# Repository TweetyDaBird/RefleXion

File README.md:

# RefleXion
 Ortho Split Keyboard

 -------------

This is a joint project with concept by The Reflex (Pedro Quaresma), and design by TweetyDaBird (Markus Knutsson).

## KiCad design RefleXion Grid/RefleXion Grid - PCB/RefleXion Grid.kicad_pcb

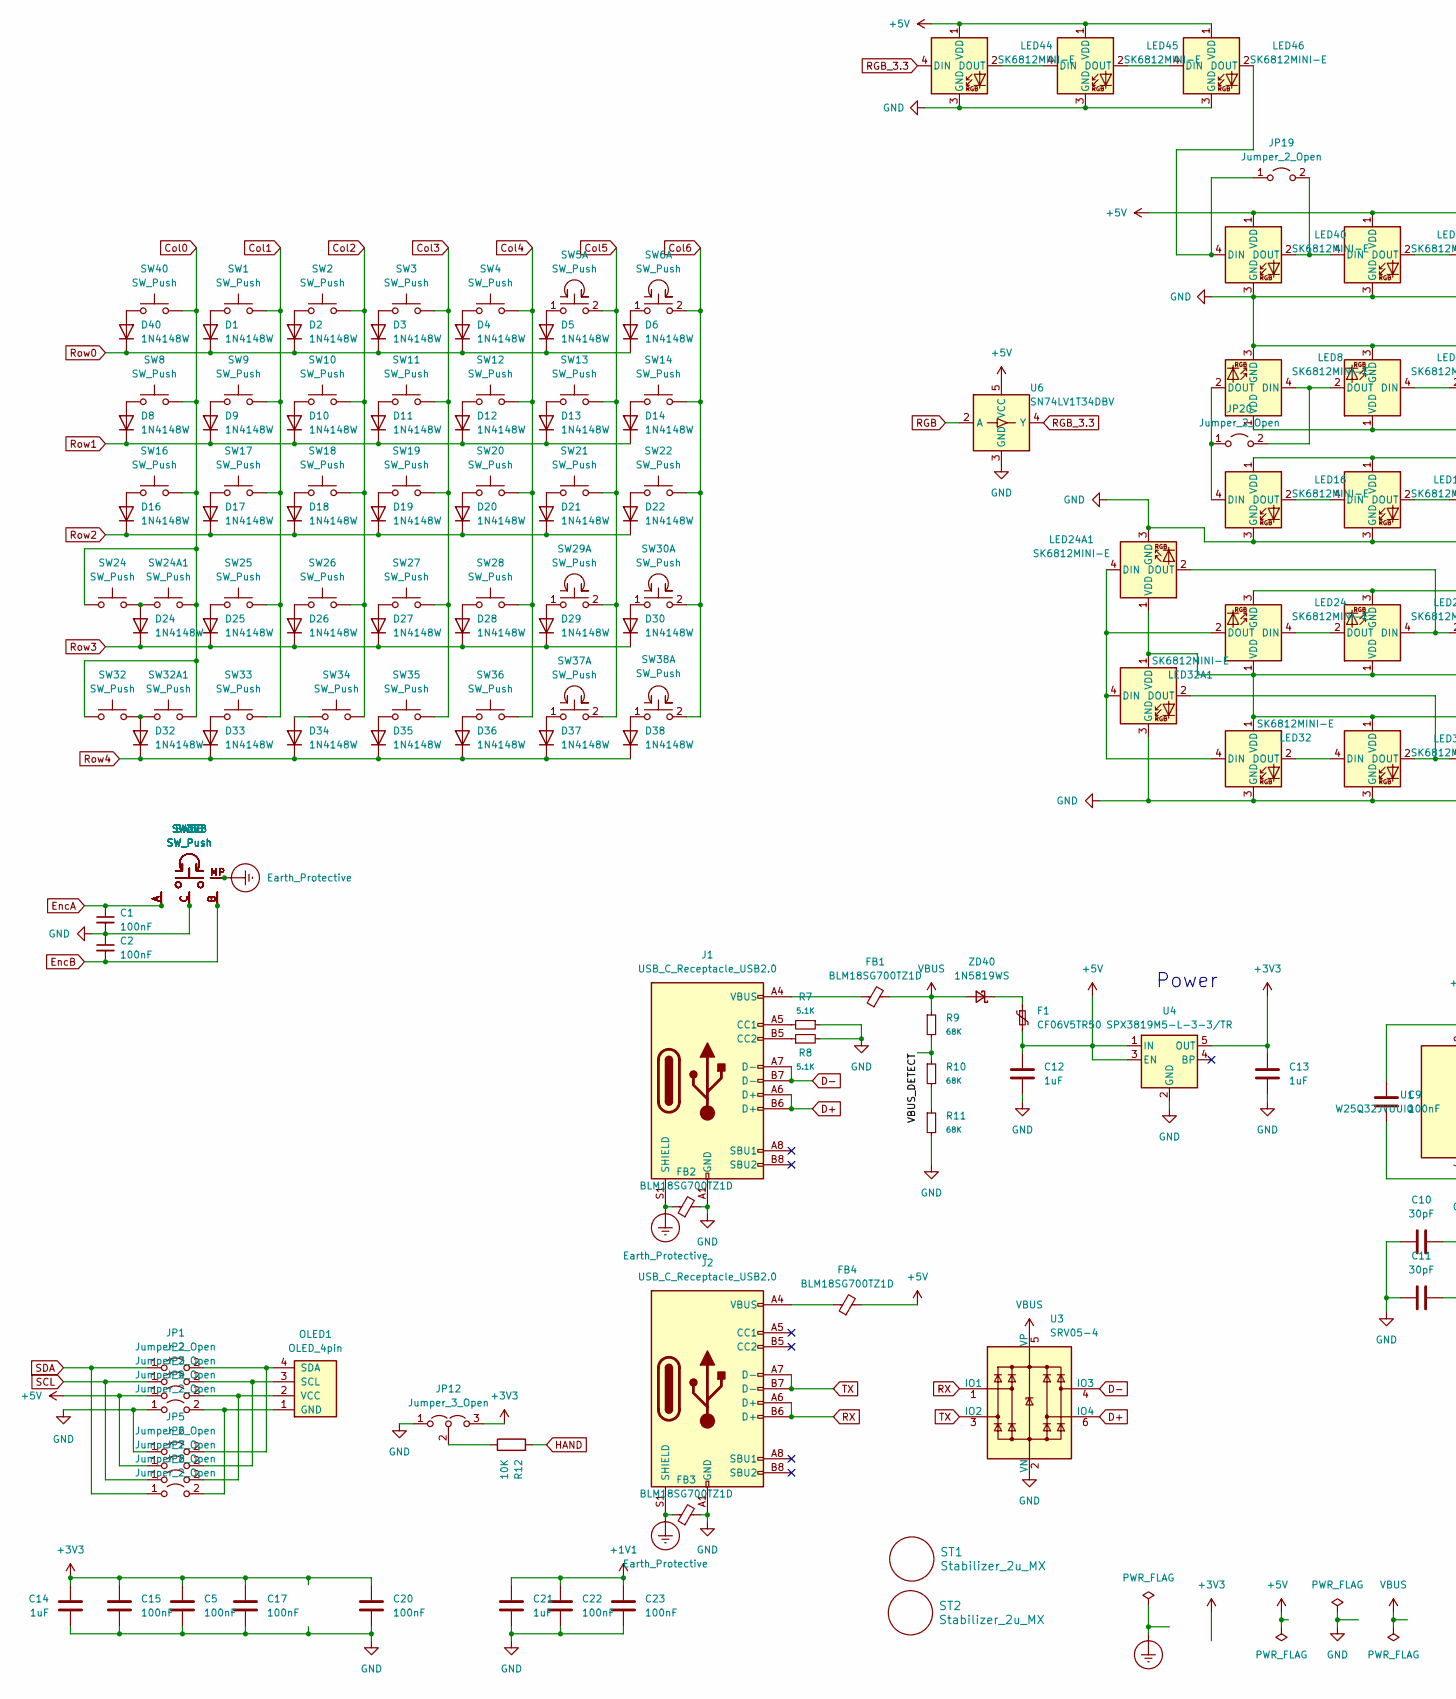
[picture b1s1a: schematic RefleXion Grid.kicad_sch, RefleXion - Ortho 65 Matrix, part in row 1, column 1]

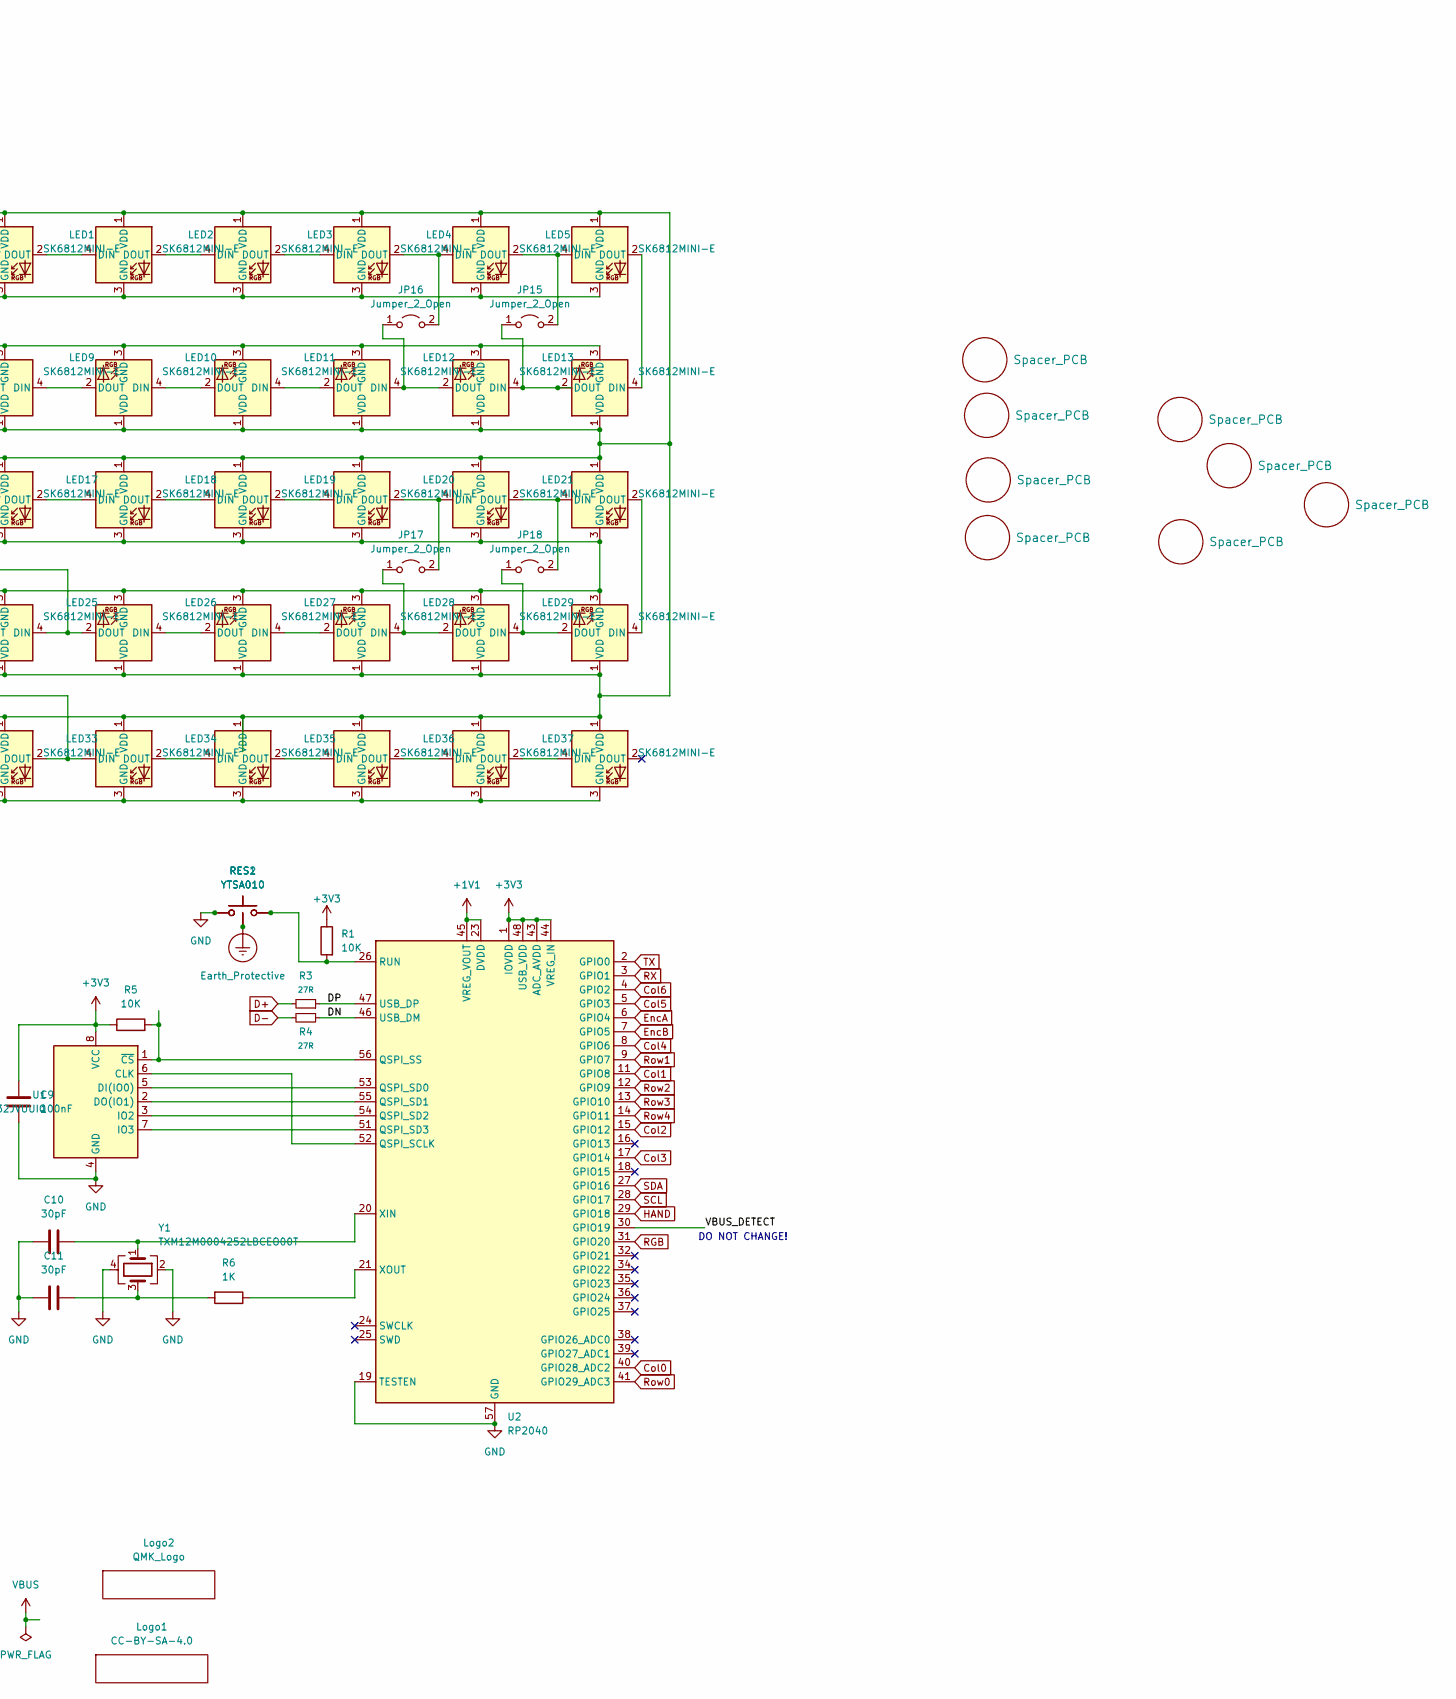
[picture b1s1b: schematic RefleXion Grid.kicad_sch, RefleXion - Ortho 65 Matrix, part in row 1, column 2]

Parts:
C1, C2: 100nF; C_0402_1005Metric
C5, C9, C15, C17, C20, C22, C23: 100nF; C_0402_1005Metric; LCSC C513772
C10, C11: 30pF; C_0402_1005Metric
C12, C13, C14, C21: 1uF; C_0402_1005Metric
D1, D2, D3, D4, D5, D6, D8, D9, D10, D11, D12, D13, D14, D16, D17, D18, D19, D20, D21, D22, D24, D25, D26, D27, D28, D29, D30, D32, D33, D34, D35, D36, D37, D38, D40: 1N4148W; D_SOD-123
F1: CF06V5TR50; R_0603_1608Metric; LCSC C163116
FB1, FB2, FB3, FB4: BLM18SG700TZ1D; C_0603_1608Metric_Pad1.08x0.95mm_HandSolder; LCSC C882974
H1, H2, H3, H4, H6, H7, H8, H9: Spacer_PCB; Spacer PCB hole
J1, J2: USB_C_Receptacle_USB2.0; Molex-216990_GCT-USB45xx_HRO-TYPE-C-31-M-13x-PiMicro; LCSC C165948
JP1, JP2, JP3, JP4, JP5, JP6, JP7, JP8, JP15, JP16, JP17, JP18, JP19, JP20: Jumper_2_Open; Jumper_min_v2
JP12: Jumper_3_Open; SolderJumper-3_open_mini
LED1, LED2, LED3, LED4, LED5, LED6, LED8, LED9, LED10, LED11, LED12, LED13, LED14, LED16, LED17, LED18, LED19, LED20, LED21, LED22, LED24, LED24A1, LED25, LED26, LED27, LED28, LED29, LED30, LED32, LED32A1, LED33, LED34, LED35, LED36, LED37, LED38, LED40, LED44, LED45, LED46: SK6812MINI-E; MX_SK6812MINI-E_REVERSIBLE_SMALL_PAD
Logo1: CC-BY-SA-4.0; CC_BY_SA_40_line
Logo2: QMK_Logo; Powered_by_QMK
OLED1: OLED_4pin; SSD1306-0.91-OLED-4pin-128x32
R1, R5: 10K; R_0402_1005Metric; LCSC C2078429
R3, R4: 27R; R_0402_1005Metric; LCSC C1701143
R6: 1K; R_0402_1005Metric; LCSC C2139907
R7, R8: 5.1K; R_0402_1005Metric; LCSC C2075916
R9, R10, R11: 68K; R_0402_1005Metric; LCSC C2075916
R12: 10K; R_0402_1005Metric; LCSC C2139907
RES1, RES2: YTSA010; YTS-A002; LCSC C2888934
ST1, ST2: Stabilizer_2u_MX; Stabilizer_Cherry_MX_2.00u
SW1, SW2, SW3, SW4, SW8, SW9, SW10, SW11, SW12, SW13, SW14, SW16, SW17, SW18, SW19, SW20, SW21, SW22, SW24, SW24A1, SW25, SW26, SW27, SW28, SW32, SW32A1, SW33, SW34, SW35, SW36, SW40: SW_Push; SW_MX_HotSwap_Reversible
SW5, SW6, SW29, SW30, SW37, SW38: SW_Push; SW_MX_HotSwap_Reversible_Encoder
U1: W25Q32JVUUIQ; USON-8_4x3mm_P0.8mm; LCSC C2999380
U2: RP2040; QFN-56-1EP_7x7mm_P0.4mm_EP3.2x3.2mm_ThermalVias; LCSC C2040
U3: SRV05-4; SOT-23-6; LCSC C558418
U4: SPX3819M5-L-3-3/TR; SOT-23-5; LCSC C9055
U6: SN74LV1T34DBV; SOT-23-5; LCSC C100024
Y1: TXM12M0004252LBCEO00T; Crystal_SMD_2520-4Pin_2.5x2.0mm; PartNo C284156; LCSC C284156
ZD40: 1N5819WS; D_SOD-323F

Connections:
+1V1: C21.1, C22.1, C23.1, U2.23 (DVDD), U2.45 (VREG_VOUT), U2.50 (DVDD)
+3V3: C5.1, C9.1, C13.1, C14.1, C15.1, C17.1, C20.1, JP12.3 (B), R1.1, R5.1, U1.8 (VCC), U2.1 (IOVDD), U2.10 (IOVDD), U2.22 (IOVDD), U2.33 (IOVDD), U2.42 (IOVDD), U2.43 (ADC_AVDD), U2.44 (VREG_IN), U2.48 (USB_VDD), U2.49 (IOVDD), U4.5 (OUT)
+5V: C12.1, F1.2, FB4.2, JP3.1 (A), JP6.1 (A), LED1.1 (VDD), LED2.1 (VDD), LED3.1 (VDD), LED4.1 (VDD), LED5.1 (VDD), LED6.1 (VDD), LED8.1 (VDD), LED9.1 (VDD), LED10.1 (VDD), LED11.1 (VDD), LED12.1 (VDD), LED13.1 (VDD), LED14.1 (VDD), LED16.1 (VDD), LED17.1 (VDD), LED18.1 (VDD), LED19.1 (VDD), LED20.1 (VDD), LED21.1 (VDD), LED22.1 (VDD), LED24.1 (VDD), LED24A1.1 (VDD), LED25.1 (VDD), LED26.1 (VDD), LED27.1 (VDD), LED28.1 (VDD), LED29.1 (VDD), LED30.1 (VDD), LED32.1 (VDD), LED32A1.1 (VDD), LED33.1 (VDD), LED34.1 (VDD), LED35.1 (VDD), LED36.1 (VDD), LED37.1 (VDD), LED38.1 (VDD), LED40.1 (VDD), LED44.1 (VDD), LED45.1 (VDD), LED46.1 (VDD), U4.1 (IN), U4.3 (EN), U6.5 (VCC)
/DN: R4.1, U2.46 (USB_DM)
/DP: R3.1, U2.47 (USB_DP)
/VBUS_DETECT: R9.2, R10.1, U2.30 (GPIO19)
Col0: SW8.1, SW16.1, SW24.1, SW24A1.1, SW32.1, SW32A1.1, SW40.1, U2.40 (GPIO28_ADC2)
Col1: SW1.2, SW9.2, SW17.2, SW25.2, SW33.2, U2.11 (GPIO8)
Col2: SW2.2, SW10.2, SW18.2, SW26.2, SW34.2, U2.15 (GPIO12)
Col3: SW3.2, SW11.2, SW19.2, SW27.2, SW35.2, U2.17 (GPIO14)
Col4: SW4.2, SW12.2, SW20.2, SW28.2, SW36.2, U2.8 (GPIO6)
Col5: SW5.2, SW13.2, SW21.2, SW29.2, SW37.2, U2.5 (GPIO3)
Col6: SW6.2, SW14.2, SW22.2, SW30.2, SW38.2, U2.4 (GPIO2)
D+: J1.A6 (D+), J1.B6 (D+), R3.2, U3.6 (IO4)
D-: J1.A7 (D-), J1.B7 (D-), R4.2, U3.4 (IO3)
Earth_Protective: FB2.1, FB3.1, J1.S1 (SHIELD), J2.S1 (SHIELD), RES1.3, RES2.3, SW5.MP, SW6.MP, SW29.MP, SW30.MP, SW37.MP, SW38.MP
EncA: C1.1, SW5.A, SW6.A, SW29.A, SW30.A, SW37.A, SW38.A, U2.6 (GPIO4)
EncB: C2.2, SW5.B, SW6.B, SW29.B, SW30.B, SW37.B, SW38.B, U2.7 (GPIO5)
GND: C1.2, C2.1, C5.2, C9.2, C10.2, C11.2, C12.2, C13.2, C14.2, C15.2, C17.2, C20.2, C21.2, C22.2, C23.2, FB2.2, FB3.2, J1.A1 (GND), J1.A12 (GND), J1.B1 (GND), J1.B12 (GND), J2.A1 (GND), J2.A12 (GND), J2.B1 (GND), J2.B12 (GND), JP4.1 (A), JP5.1 (A), JP12.1 (A), LED1.3 (GND), LED2.3 (GND), LED3.3 (GND), LED4.3 (GND), LED5.3 (GND), LED6.3 (GND), LED8.3 (GND), LED9.3 (GND), LED10.3 (GND), LED11.3 (GND), LED12.3 (GND), LED13.3 (GND), LED14.3 (GND), LED16.3 (GND), LED17.3 (GND), LED18.3 (GND), LED19.3 (GND), LED20.3 (GND), LED21.3 (GND), LED22.3 (GND), LED24.3 (GND), LED24A1.3 (GND), LED25.3 (GND), LED26.3 (GND), LED27.3 (GND), LED28.3 (GND), LED29.3 (GND), LED30.3 (GND), LED32.3 (GND), LED32A1.3 (GND), LED33.3 (GND), LED34.3 (GND), LED35.3 (GND), LED36.3 (GND), LED37.3 (GND), LED38.3 (GND), LED40.3 (GND), LED44.3 (GND), LED45.3 (GND), LED46.3 (GND), R7.1, R8.2, R11.2, RES1.1, RES2.2, SW5.C, SW6.C, SW29.C, SW30.C, SW37.C, SW38.C, U1.4 (GND), U2.19 (TESTEN), U2.57 (GND), U3.2 (VN), U4.2 (GND), U6.3 (GND), Y1.2, Y1.4
HAND: R12.2, U2.29 (GPIO18)
unnamed: C11.1, R6.2, Y1.3
unnamed: D1.2 (A), SW1.1
unnamed: D2.2 (A), SW2.1
unnamed: D3.2 (A), SW3.1
unnamed: D4.2 (A), SW4.1
unnamed: D5.2 (A), SW5.1
unnamed: D6.2 (A), SW6.1
unnamed: D8.2 (A), SW8.2
unnamed: D9.2 (A), SW9.1
unnamed: D10.2 (A), SW10.1
unnamed: D11.2 (A), SW11.1
unnamed: D12.2 (A), SW12.1
unnamed: D13.2 (A), SW13.1
unnamed: D14.2 (A), SW14.1
unnamed: D16.2 (A), SW16.2
unnamed: D17.2 (A), SW17.1
unnamed: D18.2 (A), SW18.1
unnamed: D19.2 (A), SW19.1
unnamed: D20.2 (A), SW20.1
unnamed: D21.2 (A), SW21.1
unnamed: D22.2 (A), SW22.1
unnamed: D24.2 (A), SW24.2, SW24A1.2
unnamed: D25.2 (A), SW25.1
unnamed: D26.2 (A), SW26.1
unnamed: D27.2 (A), SW27.1
unnamed: D28.2 (A), SW28.1
unnamed: D29.2 (A), SW29.1
unnamed: D30.2 (A), SW30.1
unnamed: D32.2 (A), SW32.2, SW32A1.2
unnamed: D33.2 (A), SW33.1
unnamed: D34.2 (A), SW34.1
unnamed: D35.2 (A), SW35.1
unnamed: D36.2 (A), SW36.1
unnamed: D37.2 (A), SW37.1
unnamed: D38.2 (A), SW38.1
unnamed: D40.2 (A), SW40.2
unnamed: FB1.1, J1.A4 (VBUS), J1.A9 (VBUS), J1.B4 (VBUS), J1.B9 (VBUS)
unnamed: FB4.1, J2.A4 (VBUS), J2.A9 (VBUS), J2.B4 (VBUS), J2.B9 (VBUS)
unnamed: J1.A5 (CC1), R7.2
unnamed: J1.B5 (CC2), R8.1
unnamed: JP1.2 (B), JP5.2 (B), OLED1.4 (SDA)
unnamed: JP2.2 (B), JP6.2 (B), OLED1.3 (SCL)
unnamed: JP3.2 (B), JP7.2 (B), OLED1.2 (VCC)
unnamed: JP4.2 (B), JP8.2 (B), OLED1.1 (GND)
unnamed: JP12.2 (C), R12.1
unnamed: JP15.1 (A), LED13.4 (DIN), LED14.2 (DOUT)
unnamed: JP15.2 (B), LED5.2 (DOUT), LED6.4 (DIN)
unnamed: JP16.1 (A), LED12.4 (DIN), LED13.2 (DOUT)
unnamed: JP16.2 (B), LED4.2 (DOUT), LED5.4 (DIN)
unnamed: JP17.1 (A), LED28.4 (DIN), LED29.2 (DOUT)
unnamed: JP17.2 (B), LED20.2 (DOUT), LED21.4 (DIN)
unnamed: JP18.1 (A), LED29.4 (DIN), LED30.2 (DOUT)
unnamed: JP18.2 (B), LED21.2 (DOUT), LED22.4 (DIN)
unnamed: JP19.1 (A), LED40.4 (DIN), LED46.2 (DOUT)
unnamed: JP19.2 (B), LED1.4 (DIN), LED40.2 (DOUT)
unnamed: JP20.1 (A), LED8.2 (DOUT), LED16.4 (DIN)
unnamed: JP20.2 (B), LED8.4 (DIN), LED9.2 (DOUT)
unnamed: LED1.2 (DOUT), LED2.4 (DIN)
unnamed: LED2.2 (DOUT), LED3.4 (DIN)
unnamed: LED3.2 (DOUT), LED4.4 (DIN)
unnamed: LED10.4 (DIN), LED11.2 (DOUT)
unnamed: LED9.4 (DIN), LED10.2 (DOUT)
unnamed: LED11.4 (DIN), LED12.2 (DOUT)
unnamed: LED6.2 (DOUT), LED14.4 (DIN)
unnamed: LED16.2 (DOUT), LED17.4 (DIN)
unnamed: LED17.2 (DOUT), LED18.4 (DIN)
unnamed: LED18.2 (DOUT), LED19.4 (DIN)
unnamed: LED19.2 (DOUT), LED20.4 (DIN)
unnamed: LED22.2 (DOUT), LED30.4 (DIN)
unnamed: LED24.4 (DIN), LED25.2 (DOUT)
unnamed: LED24.2 (DOUT), LED24A1.4 (DIN), LED32.4 (DIN), LED32A1.4 (DIN)
unnamed: LED24A1.2 (DOUT), LED25.4 (DIN), LED26.2 (DOUT)
unnamed: LED26.4 (DIN), LED27.2 (DOUT)
unnamed: LED27.4 (DIN), LED28.2 (DOUT)
unnamed: LED32.2 (DOUT), LED33.4 (DIN)
unnamed: LED32A1.2 (DOUT), LED33.2 (DOUT), LED34.4 (DIN)
unnamed: LED34.2 (DOUT), LED35.4 (DIN)
unnamed: LED35.2 (DOUT), LED36.4 (DIN)
unnamed: LED36.2 (DOUT), LED37.4 (DIN)
unnamed: LED37.2 (DOUT), LED38.4 (DIN)
unnamed: LED44.2 (DOUT), LED45.4 (DIN)
unnamed: LED45.2 (DOUT), LED46.4 (DIN)
unnamed: R10.2, R11.1
unnamed: U1.6 (CLK), U2.52 (QSPI_SCLK)
unnamed: U1.5 (DI(IO0)), U2.53 (QSPI_SD0)
unnamed: U1.2 (DO(IO1)), U2.55 (QSPI_SD1)
unnamed: U1.3 (IO2), U2.54 (QSPI_SD2)
unnamed: U1.7 (IO3), U2.51 (QSPI_SD3)
unnamed: R5.2, U1.1 (~CS), U2.56 (QSPI_SS)
unnamed: R1.2, RES1.2, RES2.1, U2.26 (RUN)
unnamed: C10.1, U2.20 (XIN), Y1.1
unnamed: R6.1, U2.21 (XOUT)
unnamed: F1.1, ZD40.1 (K)
RGB: U2.31 (GPIO20), U6.2 (A)
RGB_3.3: LED44.4 (DIN), U6.4 (Y)
RX: J2.A6 (D+), J2.B6 (D+), U2.3 (GPIO1), U3.1 (IO1)
Row0: D1.1 (K), D2.1 (K), D3.1 (K), D4.1 (K), D5.1 (K), D6.1 (K), D40.1 (K), U2.41 (GPIO29_ADC3)
Row1: D8.1 (K), D9.1 (K), D10.1 (K), D11.1 (K), D12.1 (K), D13.1 (K), D14.1 (K), U2.9 (GPIO7)
Row2: D16.1 (K), D17.1 (K), D18.1 (K), D19.1 (K), D20.1 (K), D21.1 (K), D22.1 (K), U2.12 (GPIO9)
Row3: D24.1 (K), D25.1 (K), D26.1 (K), D27.1 (K), D28.1 (K), D29.1 (K), D30.1 (K), U2.13 (GPIO10)
Row4: D32.1 (K), D33.1 (K), D34.1 (K), D35.1 (K), D36.1 (K), D37.1 (K), D38.1 (K), U2.14 (GPIO11)
SCL: JP2.1 (A), JP7.1 (A), U2.28 (GPIO17)
SDA: JP1.1 (A), JP8.1 (A), U2.27 (GPIO16)
TX: J2.A7 (D-), J2.B7 (D-), U2.2 (GPIO0), U3.3 (IO2)
VBUS: FB1.2, R9.1, U3.5 (VP), ZD40.2 (A)

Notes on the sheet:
Power
DO NOT CHANGE!

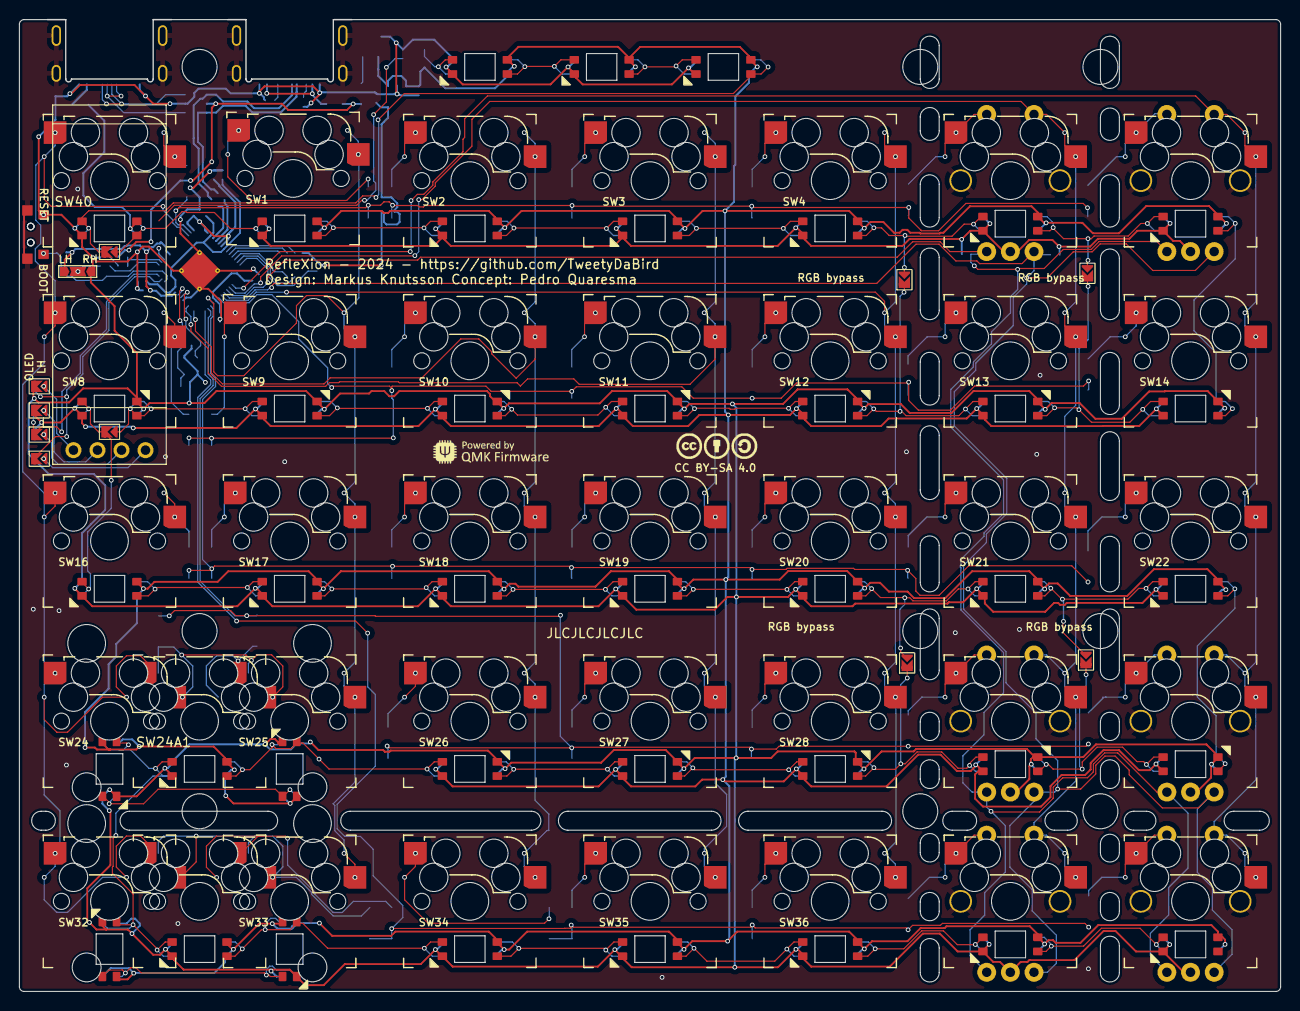
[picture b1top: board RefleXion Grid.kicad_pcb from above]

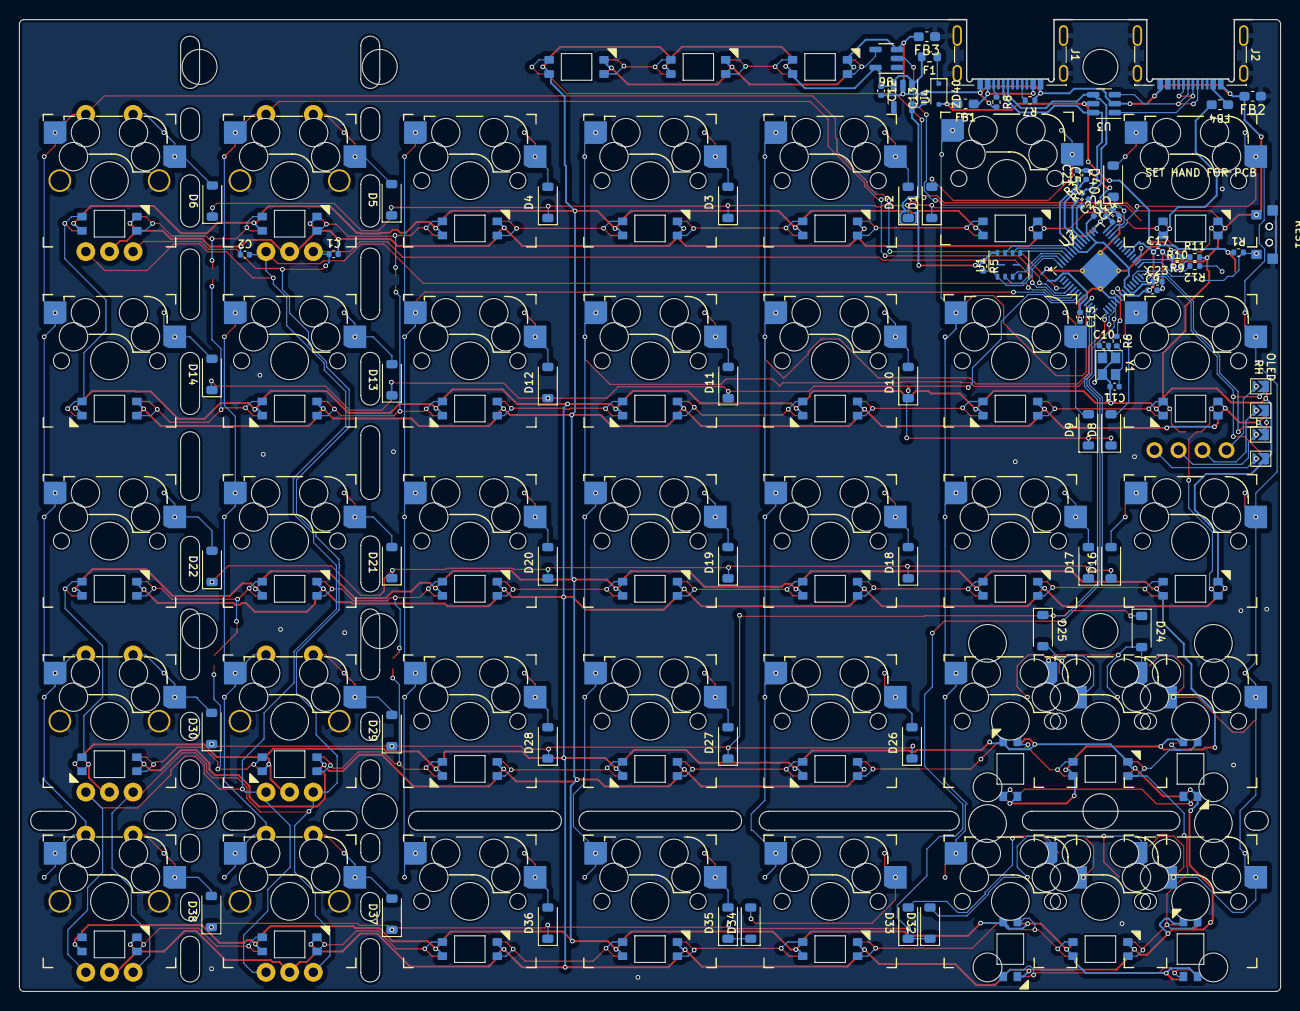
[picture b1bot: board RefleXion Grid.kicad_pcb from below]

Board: 2 copper layers, 133.4 x 102.7 mm, 183 parts (81 on the bottom side), 125 nets.

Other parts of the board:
H4#2: Spacer_PCB; Spacer PCB hole

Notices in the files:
RefleXion - Large Module/RefleXion - Large Module.kicad_pcb:
Licensed under Creative Commons BY-SA 4.0 International
